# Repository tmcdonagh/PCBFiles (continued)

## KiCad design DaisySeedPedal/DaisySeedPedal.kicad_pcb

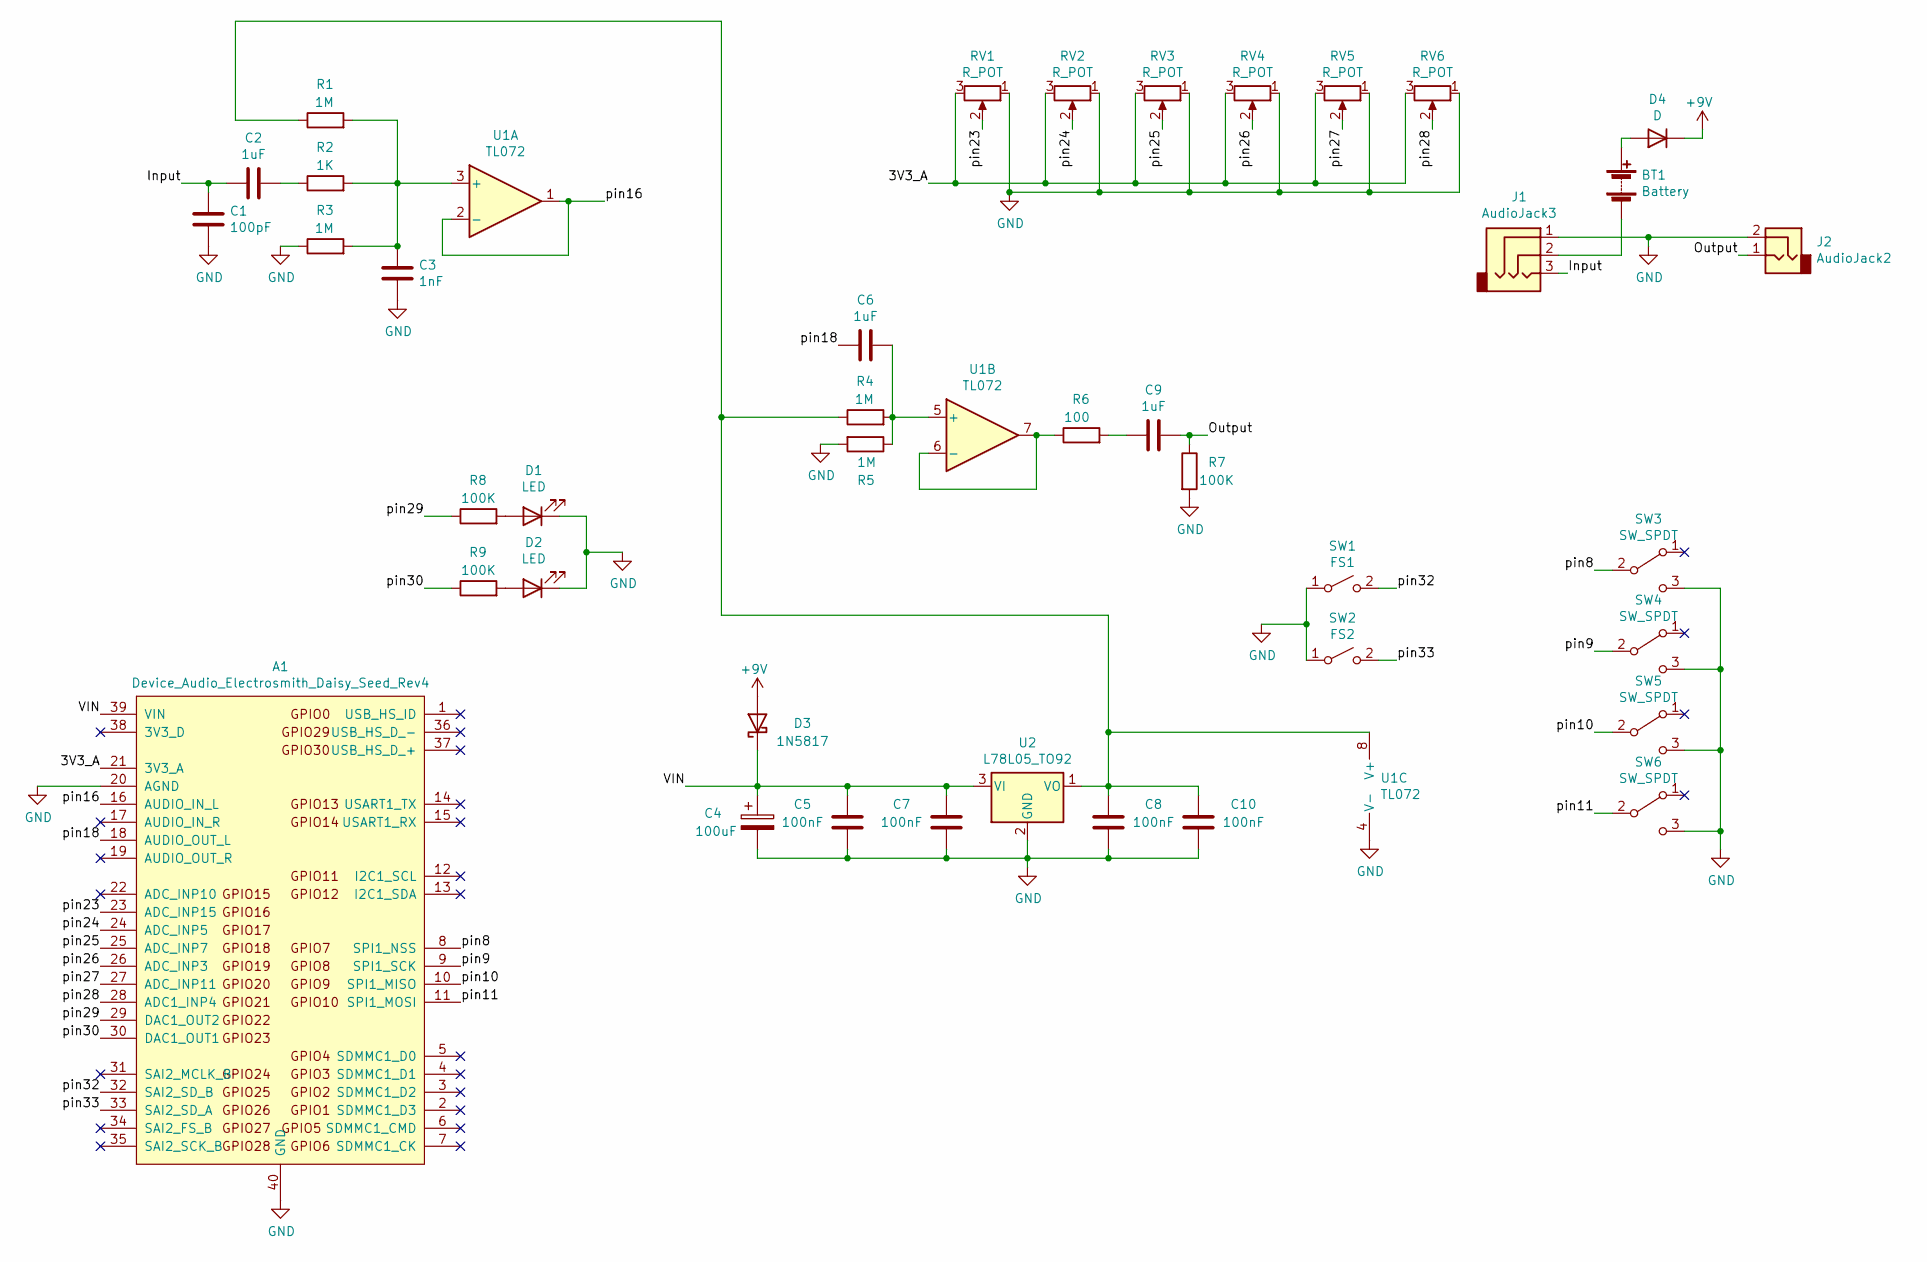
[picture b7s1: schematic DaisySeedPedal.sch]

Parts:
A1: Device_Audio_Electrosmith_Daisy_Seed_Rev4; Device_Audio_Electrosmith_Daisy_Seed
BT1: Battery; PinSocket_1x02_P2.54mm_Vertical
C1: 100pF; C_Axial_L3.8mm_D2.6mm_P7.50mm_Horizontal
C2, C6, C9: 1uF; C_Flat_L7.2_H10
C3: 1nF; C_Flat_L7.2_H6.5
C4: 100uF; CP_Radial_D6.3mm_P2.00mm_L11.0mm
C5, C7, C8, C10: 100nF; C_Flat_L7.2_H6.5
D1, D2: LED; LED_D5.0mm
D3: 1N5817; D_DO-41_SOD81_P10.16mm_Horizontal
D4: D; D_DO-41_SOD81_P10.16mm_Horizontal
J1: AudioJack3; PinSocket_1x03_P2.54mm_Vertical
J2: AudioJack2; PinSocket_1x02_P2.54mm_Vertical
R1, R3, R4, R5: 1M; R_Axial_DIN0207_L6.3mm_D2.5mm_P10.16mm_Horizontal
R2: 1K; R_Axial_DIN0207_L6.3mm_D2.5mm_P10.16mm_Horizontal
R6: 100; R_Axial_DIN0207_L6.3mm_D2.5mm_P10.16mm_Horizontal
R7, R8, R9: 100K; R_Axial_DIN0207_L6.3mm_D2.5mm_P10.16mm_Horizontal
RV1, RV2, RV3, RV4, RV5, RV6: R_POT
SW1: FS1; PinSocket_1x02_P2.54mm_Vertical
SW2: FS2; PinSocket_1x02_P2.54mm_Vertical
SW3, SW4, SW5, SW6: SW_SPDT; MSS10255914AD
U1: TL072; DIP-8_W7.62mm
U2: L78L05_TO92; TO-92_Inline_Wide

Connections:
+9V: D3.2 (A), D4.1 (K)
/3V3_A: A1.21 (3V3_A), RV1.3, RV2.3, RV3.3, RV4.3, RV5.3, RV6.3
/Input: C1.2, C2.2, J1.3
/Output: C9.1, J2.1, R7.1
/VIN: A1.39 (VIN), C4.1, C5.1, C7.1, D3.1 (K), U2.3 (VI)
/pin8: A1.8 (SPI1_NSS), SW3.2 (B)
/pin9: A1.9 (SPI1_SCK), SW4.2 (B)
/pin10: A1.10 (SPI1_MISO), SW5.2 (B)
/pin11: A1.11 (SPI1_MOSI), SW6.2 (B)
/pin16: A1.16 (AUDIO_IN_L), U1.1, U1.2 (-)
/pin18: A1.18 (AUDIO_OUT_L), C6.2
/pin23: A1.23 (ADC_INP15), RV1.2
/pin24: A1.24 (ADC_INP5), RV2.2
/pin25: A1.25 (ADC_INP7), RV3.2
/pin26: A1.26 (ADC_INP3), RV4.2
/pin27: A1.27 (ADC_INP11), RV5.2
/pin28: A1.28 (ADC1_INP4), RV6.2
/pin29: A1.29 (DAC1_OUT2), R8.1
/pin30: A1.30 (DAC1_OUT1), R9.1
/pin32: A1.32 (SAI2_SD_B), SW1.2 (B)
/pin33: A1.33 (SAI2_SD_A), SW2.2 (B)
GND: A1.20 (AGND), A1.40 (GND), C1.1, C3.1, C4.2, C5.2, C7.2, C8.1, C10.1, D1.1 (K), D2.1 (K), J1.1, J2.2, R3.1, R5.2, R7.2, RV1.1, RV2.1, RV3.1, RV4.1, RV5.1, RV6.1, SW1.1 (A), SW2.1 (A), SW3.3 (C), SW4.3 (C), SW5.3 (C), SW6.3 (C), U1.4 (V-), U2.2 (GND)
unnamed: BT1.1 (+), D4.2 (A)
unnamed: BT1.2 (-), J1.2
unnamed: C2.1, R2.1
unnamed: C3.2, R1.2, R2.2, R3.2, U1.3 (+)
unnamed: C6.1, R4.2, R5.1, U1.5 (+)
unnamed: C9.2, R6.2
unnamed: C8.2, C10.2, R1.1, R4.1, U1.8 (V+), U2.1 (VO)
unnamed: D1.2 (A), R8.2
unnamed: D2.2 (A), R9.2
unnamed: R6.1, U1.6 (-), U1.7

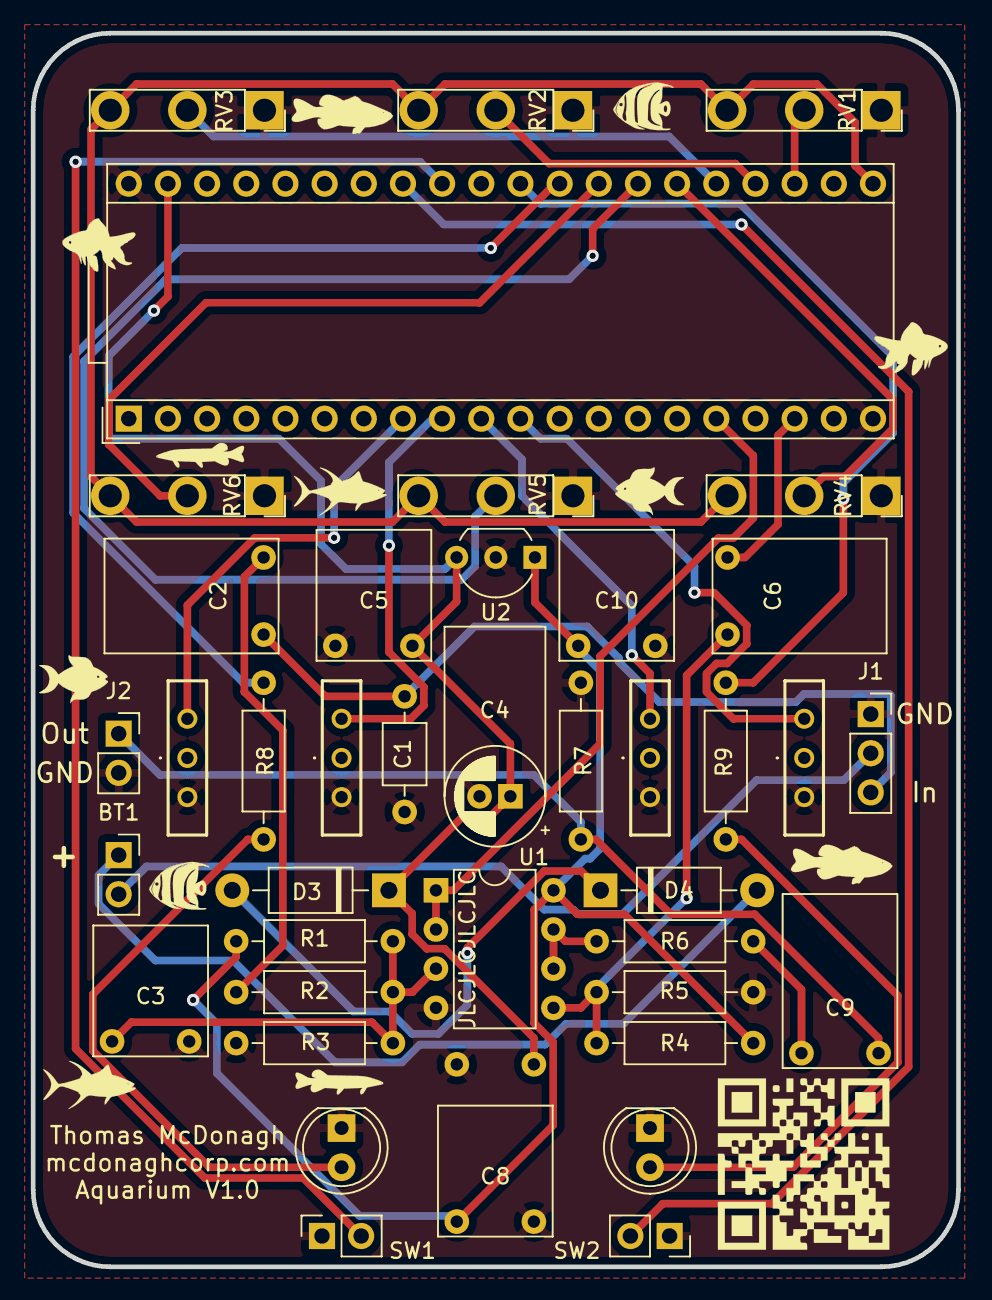
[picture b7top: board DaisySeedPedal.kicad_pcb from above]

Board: 2 copper layers, 60.0 x 80.0 mm, 41 parts (1 on the bottom side), 32 nets.

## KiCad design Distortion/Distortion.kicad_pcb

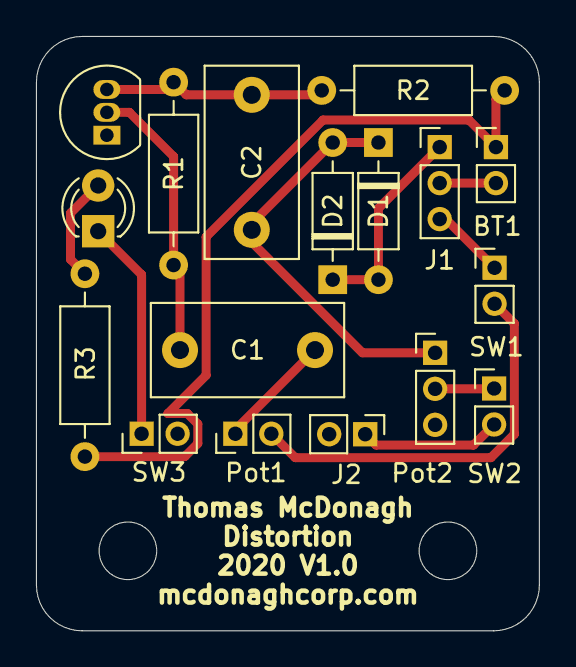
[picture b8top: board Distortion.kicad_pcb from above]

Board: 2 copper layers, 27.9 x 33.0 mm, 17 parts (0 on the bottom side), 13 nets.

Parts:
BT1: Battery; PinHeader_1x02_P2.00mm_Vertical
C1, C2: C; C_Disc_D10.5mm_W5.0mm_P7.50mm
D1, D2: 1N4148; D_DO-35_SOD27_P7.62mm_Horizontal
D3: LED; LED_D3.0mm_Clear
J1: AudioJack3; PinHeader_1x03_P2.00mm_Vertical
J2: AudioJack2; PinHeader_1x02_P2.00mm_Vertical
Pot1: R_POT; PinHeader_1x02_P2.00mm_Vertical
Pot2: R_POT; PinHeader_1x03_P2.00mm_Vertical
Q1: 2N3904; TO-92_Inline
R1, R2, R3: R; R_Axial_DIN0207_L6.3mm_D2.5mm_P10.16mm_Horizontal
SW1, SW2, SW3: SW_SPST; PinHeader_1x02_P2.00mm_Vertical

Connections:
GND: D1.2, D2.1, J1.1, J2.2, Pot2.3, Q1.1, SW3.2
unnamed: BT1.1, R2.2, R3.1
unnamed: BT1.2, J1.2
unnamed: C1.1, Q1.2, R1.1
unnamed: C1.2, Pot1.1
unnamed: C2.1, D1.1, D2.2, Pot2.1
unnamed: C2.2, Q1.3, R1.2, R2.1
unnamed: D3.1, SW3.1
unnamed: D3.2, R3.2
unnamed: J1.3, SW1.1
unnamed: J2.1, SW2.2
unnamed: Pot1.2, SW1.2
unnamed: Pot2.2, SW2.1
